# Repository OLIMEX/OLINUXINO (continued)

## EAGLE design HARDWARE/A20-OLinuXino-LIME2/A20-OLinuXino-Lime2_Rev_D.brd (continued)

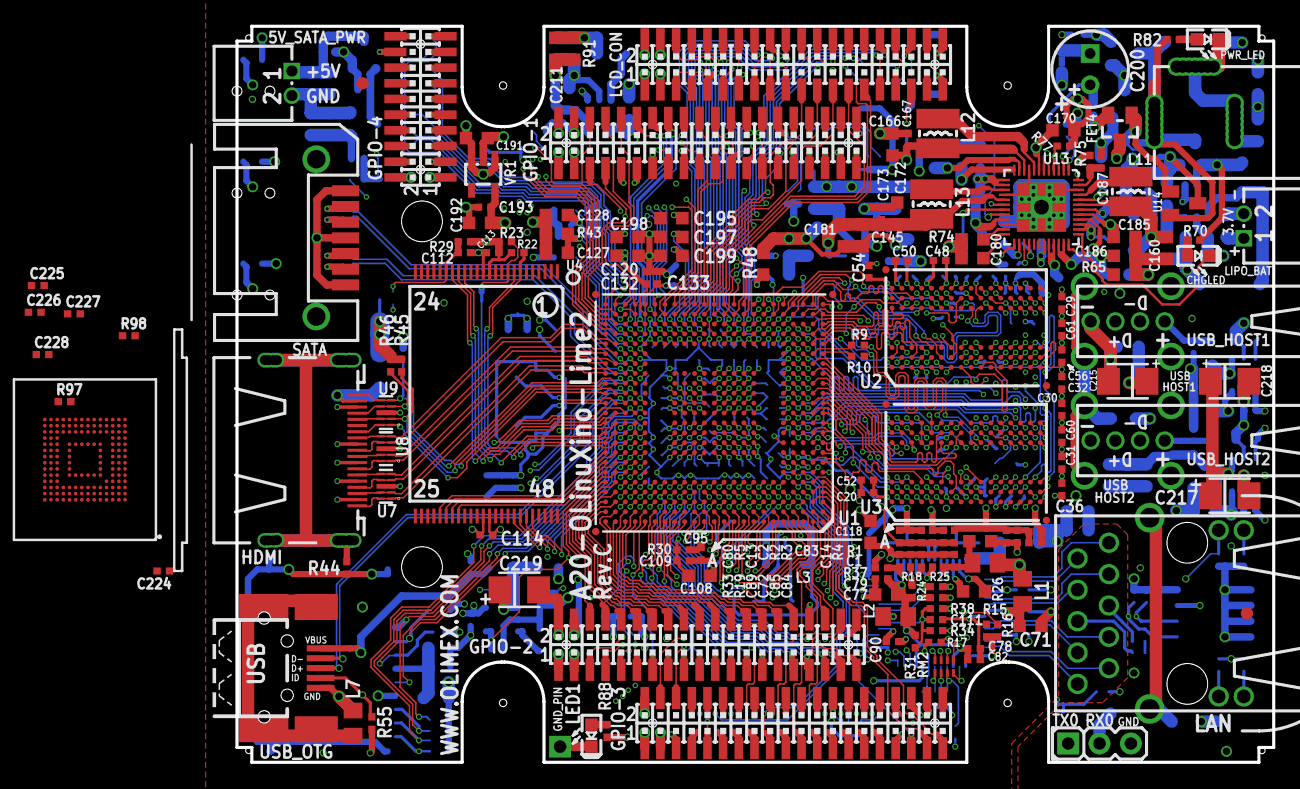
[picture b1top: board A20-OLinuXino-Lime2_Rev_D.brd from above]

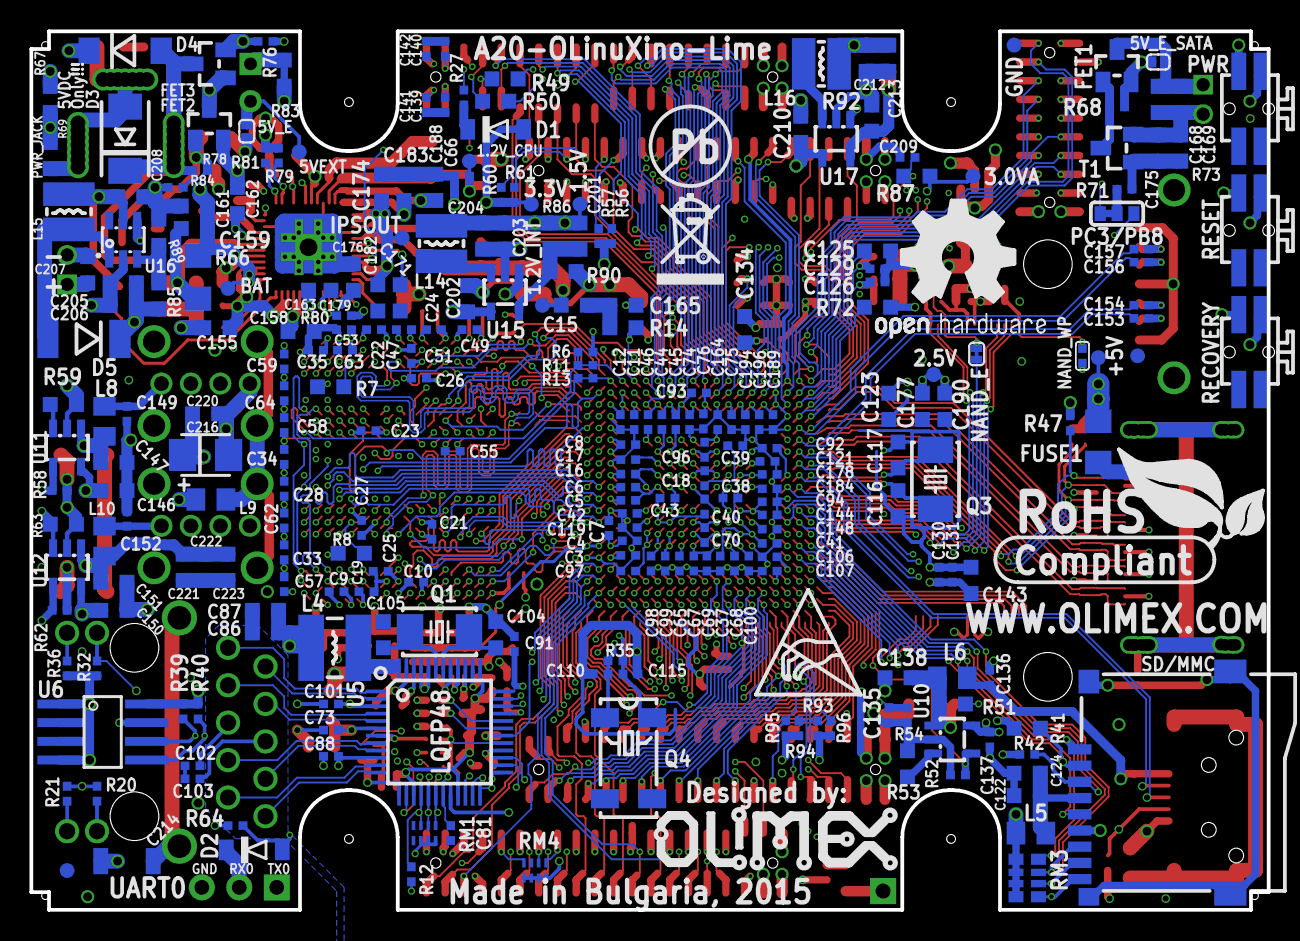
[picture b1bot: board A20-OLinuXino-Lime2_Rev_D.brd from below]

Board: 8 copper layers, 84.0 x 59.6 mm, 428 parts (274 on the bottom side), 425 nets.

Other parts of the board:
NAND_WP: NA; R0402_TI
U$2: HAMMOND_1593LBK_A10_LIME
U$5: LOGO-OPENHARDWARE_8X8
U$6: OLIMEX1_V
U$9: PB
U$10: ESD_SYMBOL
U$11: RECYCLE_BIN1/8
U$12: ROHS

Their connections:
unnamed 197: NAND_WP.2; also elsewhere on the board
PC16/NWP: NAND_WP.1; also elsewhere on the board
